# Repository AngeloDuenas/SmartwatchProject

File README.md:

# LVGL project for ESP32

This is an ESP32 demo project showcasing LVGL v7 with support for several display controllers and touch controllers.
The demo application is the `lv_demo_widgets` project from the [lv_examples](https://github.com/lvgl/lv_examples) repository.

- Version of ESP-IDF required 4.2. NOTE: We're trying to make this repo backwards compatible, usage of idf.py is encouraged.
- Version of LVGL used: 7.9.
- Version of lv_examples used: 7.9.

#### Table of content
- [Get started](#get-started)
- [Use LVGL in your ESP-IDF project](#use-lvgl-in-your-esp-idf-project)
- [Use lvgl_esp32_drivers in your project](#use-lvgl_esp32_drivers-in-your-project)
- [Platformio support](#platformio-support)
- [ESP32-S2 Support](#esp32-s2-support)

Example demo for TFT displays:

Monochrome support:

## Display and touch controllers

The display and touch (indev) controllers are now into it's own repository, you can find it [here](https://github.com/lvgl/lvgl_esp32_drivers).
To report any issue or add new display or touch (indev) drivers you can do so in the `lvgl_esp32_drivers` repo.

## Get started

### Prerequisites

- ESP-IDF Framework.

### Note

This project tries to be compatible with both the ESP-IDF v3.x and v4.0, but using v4.0 is recommended.
Instructions assume you are using the v4.x toolchain, otherwise use the make commands, e.g. instead of running `idf.py menuconfig`, run `make menuconfig`.

### Build and run the demo.

1. Clone this project by `git clone --recurse-submodules https://github.com/lvgl/lv_port_esp32.git`, this will pull this repo and its submodules.

2. Get into the created `lv_port_esp32` directory.

3. Run `idf.py menuconfig`

4. Configure LVGL in `Components config->LVGL Configuration`. For monochrome displays use the mono theme and we suggest enabling the `unscii 8` font.

5. Configure your display and/or touch controllers in `Components config->LVGL TFT Display Configuration` and `Components config->LVGL TOUCH Configuration`.

6. Store your project configuration.

7. Build the project with `idf.py build`

8. If the build don't throw any errors, flash the demo with `idf.py -p (YOUR SERIAL PORT) flash` (with `make` this is just `make flash` - in 3.x PORT is configured in `menuconfig`)

## Use LVGL in your ESP-IDF project

LVGL now includes a Kconfig file which is used to configure most of the LVGL configuration options via menuconfig, so it's not necessary to use a custom `lv_conf.h` file.

It is recommended to add LVGL as a submodule in your IDF project's git repo.

From your project's root directory:
1. Create a directory named `components` (if you don't have one already) with `mkdir -p components`.
2. Clone the lvgl repository inside the `components` directory with `git submodule add https://github.com/lvgl/lvgl.git components/lvgl`
3. Run `idf.py menuconfig`, go to `Component config` then `LVGL configuration` to configure LVGL.

## Use lvgl_esp32_drivers in your project

It is recommended to add [lvgl_esp32_drivers](https://github.com/lvgl/lvgl_esp32_drivers) as a submodule in your IDF project's git repo.

From your project's root directory:
1. Create a directory named `components` (if you don't have one already) with `mkdir -p components`.
2. Clone the lvgl_esp32_drivers repository inside the `components` directory with `git submodule add https://github.com/lvgl/lvgl_esp32_drivers.git components/lvgl_esp32_drivers`
3. Run `idf.py menuconfig`, go to `Component config` then `LVGL TFT configuration` and `LVGL TFT Display configuration` to configure lvgl_esp32_drivers.

## Platformio support

Using the [lv_platformio](https://github.com/lvgl/lv_platformio) project add the following lines to `platformio.ini` file:

```
[env:esp32]
platform = espressif32
framework = espidf
board = esp-wrover-kit
```

Change the default environment to `default_envs = esp32`.

Modify the `main.c` like this:

```c
#include "lvgl.h"

// #include "driver.h"

#include "demo.h"

int app_main(void)
{
    lv_init();

    /* Initialize your hardware. */
    
    /* hw_init(); */

    demo_create();

    /* Create the UI or start a task for it.
     * In the end, don't forget to call `lv_task_handler` in a loop. */

    /* hw_loop(); */

    return 0;
}
```

For more information see: [platformio with espidf framework compability](https://github.com/lvgl/lv_port_esp32/issues/168).

# ESP32-S2 Support

Support for ESP32-S2 variant is Work In Progress.
Smaller displays (e.g. 320x240) work fine, but larger ones need testing.

## Background

ESP32-S2 has less on-chip SRAM than its predecessor ESP32 (520kB vs. 320kB).
This causes problems with memory allocation with large LVGL display buffers as they don't fit into the on-chip memory
and external PSRAM is not accessible by DMA.

Moreover, static allocation to external PSRAM is not yet supported
(see [GitHub issue](https://github.com/espressif/esp-idf/issues/6162)).

At this momement, the buffers are dynamicaly allocated with DMA capabilty and memory allocator handles the rest.

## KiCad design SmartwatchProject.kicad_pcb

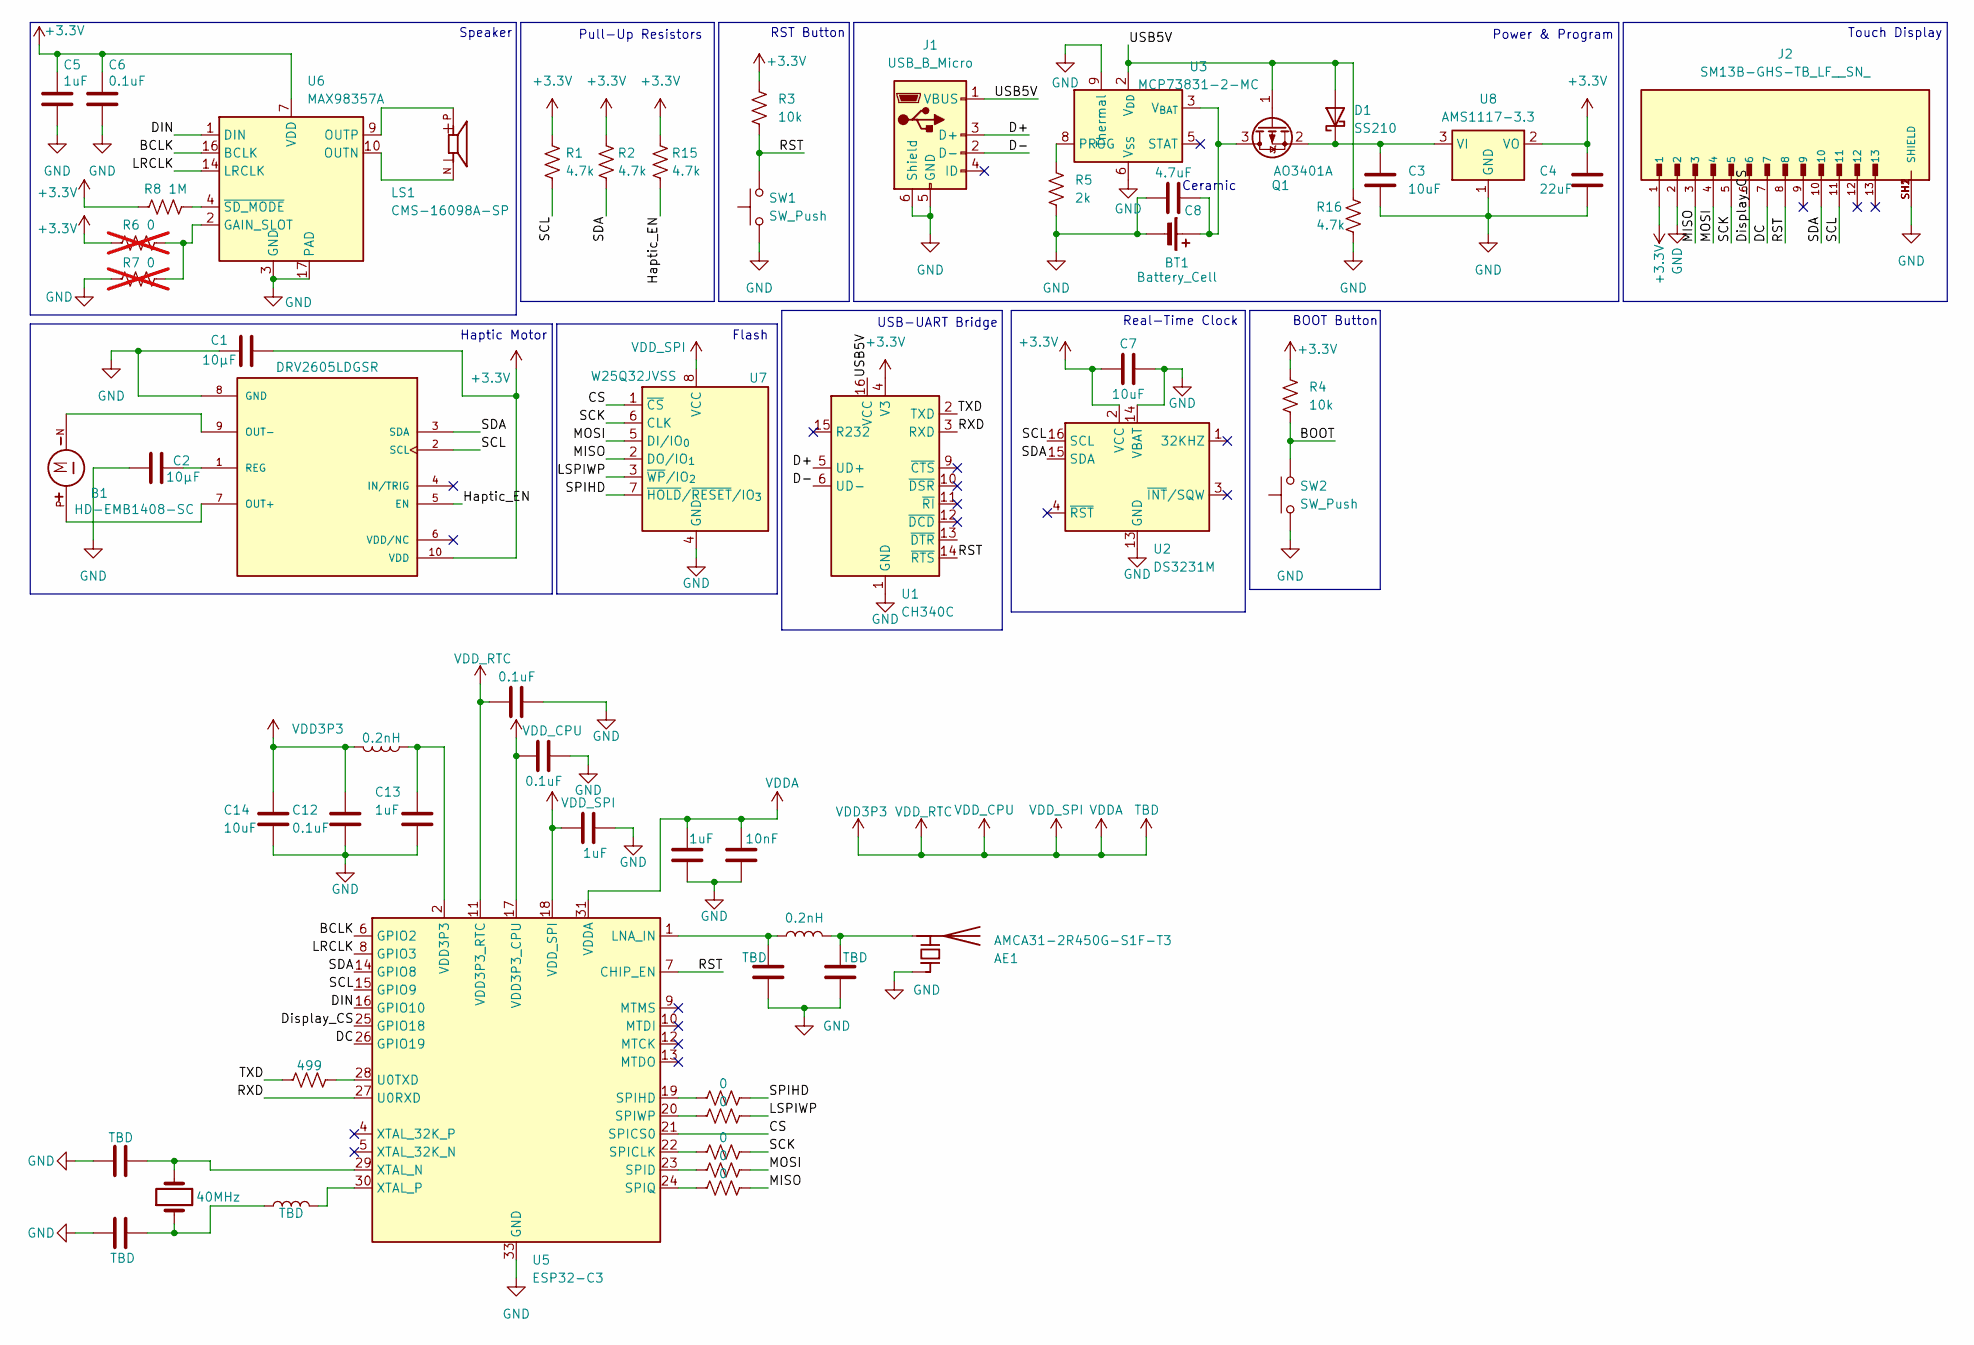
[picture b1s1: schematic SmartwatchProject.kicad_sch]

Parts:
AE1: AMCA31-2R450G-S1F-T3; XDCR_AMCA31-2R450G-S1F-T3
B1: HD-EMB1408-SC; MOTOR_HD-EMB1408-SC; PARTREV A
BT1: Battery_Cell; PinHeader_1x02_P1.00mm_Vertical
C1: 10µF; C_0603_1608Metric
C2: 10µF; C_0402_1005Metric
C3, C7, C14: 10uF; C_0402_1005Metric
C4: 22uF; C_0402_1005Metric
C5, C13, C17, C18: 1uF; C_0402_1005Metric
C6, C12, C15, C16: 0.1uF; C_0402_1005Metric
C8: 4.7uF; C_0402_1005Metric
C10, C11, C20, C21: TBD; C_0402_1005Metric
C19: 10nF; C_0402_1005Metric
D1: SS210; D_SMA
J1: USB_B_Micro; USB_Micro-B_Molex-105017-0001
J2: SM13B-GHS-TB_LF__SN_; JST_SM13B-GHS-TB_LF__SN_; PARTREV 18/3/21
L1, L2: 0.2nH; L_0402_1005Metric
L3: TBD; L_0402_1005Metric
LS1: CMS-16098A-SP; CUI_CMS-16098A-SP
Q1: AO3401A; SOT-23
R1, R2, R15, R16: 4.7k; R_0402_1005Metric
R3, R4: 10k; R_0402_1005Metric
R5: 2k; R_0402_1005Metric
R6, R7: 0; R_0402_1005Metric; not fitted
R8: 1M; R_0402_1005Metric
R9, R10, R11, R12, R13: 0; R_0402_1005Metric
R14: 499; R_0402_1005Metric
SW1, SW2: SW_Push; SW_SPST_TL3342
U1: CH340C; SOIC-16_3.9x9.9mm_P1.27mm
U2: DS3231M; SOIC-16W_7.5x10.3mm_P1.27mm
U3: MCP73831-2-MC; DFN-8-1EP_3x2mm_P0.5mm_EP1.7x1.4mm
U4: DRV2605LDGSR; SOP50P490X110-10N; PARTREV D
U5: ESP32-C3; QFN-32-1EP_5x5mm_P0.5mm_EP3.7x3.7mm
U6: MAX98357A; TQFN-16-1EP_3x3mm_P0.5mm_EP1.23x1.23mm
U7: W25Q32JVSS; SOIC-8_5.3x5.3mm_P1.27mm
U8: AMS1117-3.3; SOT-223-3_TabPin2
Y1: 40MHz; Crystal_SMD_3215-2Pin_3.2x1.5mm

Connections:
+3.3V: C1.2, C4.2, C5.1, C6.1, C7.2, J2.1, R1.1, R2.1, R3.1, R4.1, R6.1, R8.1, R15.1, U1.4 (V3), U2.2 (VCC), U4.10 (VDD), U6.7 (VDD), U6.8 (VDD), U8.2 (VO)
/BCLK: U5.6 (GPIO2), U6.16 (BCLK)
/BOOT: R4.2, SW2.2
/CS: U5.21 (SPICS0), U7.1 (~CS)
/D+: J1.3 (D+), U1.5 (UD+)
/D-: J1.2 (D-), U1.6 (UD-)
/DC: J2.7, U5.26 (GPIO19)
/DIN: U5.16 (GPIO10), U6.1 (DIN)
/Display_CS: J2.6, U5.25 (GPIO18)
/Haptic_EN: R15.2, U4.5 (EN)
/LRCLK: U5.8 (GPIO3), U6.14 (LRCLK)
/LSPIWP: R10.2, U7.3 (~WP/IO_{2})
/MISO: J2.3, R13.2, U7.2 (DO/IO_{1})
/MOSI: J2.4, R12.2, U7.5 (DI/IO_{0})
/RST: J2.8, R3.2, SW1.2, U1.14 (~RTS), U5.7 (CHIP_EN)
/RXD: U1.3 (RXD), U5.27 (U0RXD)
/SCK: J2.5, R11.2, U7.6 (CLK)
/SCL: J2.11, R1.2, U2.16 (SCL), U4.2 (SCL), U5.15 (GPIO9)
/SDA: J2.10, R2.2, U2.15 (SDA), U4.3 (SDA), U5.14 (GPIO8)
/SPIHD: R9.2, U7.7 (~HOLD/~RESET/IO_{3})
/TXD: R14.1, U1.2 (TXD)
/USB5V: D1.2 (A), J1.1 (VBUS), Q1.1 (G), R16.1, U1.16 (VCC), U3.1 (V_{DD}), U3.2 (V_{DD})
GND: AE1.1 (FEED), BT1.2 (-), C1.1, C2.1, C3.2, C4.1, C5.2, C6.2, C7.1, C8.2, C10.2, C11.2, C12.2, C13.2, C14.2, C15.2, C16.2, C17.2, C18.1, C19.1, C20.2, C21.2, J1.5 (GND), J1.6 (Shield), J2.2, J2.SH1 (SHIELD), J2.SH2 (SHIELD), R5.2, R7.1, R16.2, SW1.1, SW2.1, U1.1 (GND), U2.5 (GND), U2.6 (GND), U2.7 (GND), U2.8 (GND), U2.9 (GND), U2.10 (GND), U2.11 (GND), U2.12 (GND), U2.13 (GND), U2.14 (VBAT), U3.6 (V_{SS}), U3.9 (Thermal), U4.8 (GND), U5.33 (GND), U6.3 (GND), U6.11 (GND), U6.15 (GND), U6.17 (PAD), U7.4 (GND), U8.1 (GND)
unnamed: AE1.2 (PCB_Trace), C11.1, L1.2
unnamed: BT1.1 (+), C8.1, Q1.3 (D), U3.3 (V_{BAT}), U3.4 (V_{BAT})
unnamed: C13.1, L2.1, U5.2 (VDD3P3), U5.3 (VDD3P3)
unnamed: C21.1, L3.1, Y1.1
unnamed: C3.1, D1.1 (K), Q1.2 (S), U8.3 (VI)
unnamed: R5.1, U3.8 (PROG)
unnamed: B1.P, U4.7 (OUT+)
unnamed: B1.N, U4.9 (OUT-)
unnamed: C2.2, U4.1 (REG)
unnamed: C10.1, L1.1, U5.1 (LNA_IN)
unnamed: R11.1, U5.22 (SPICLK)
unnamed: R12.1, U5.23 (SPID)
unnamed: R9.1, U5.19 (SPIHD)
unnamed: R13.1, U5.24 (SPIQ)
unnamed: R10.1, U5.20 (SPIWP)
unnamed: R14.2, U5.28 (U0TXD)
unnamed: C20.1, U5.29 (XTAL_N), Y1.2
unnamed: L3.2, U5.30 (XTAL_P)
unnamed: R6.2, R7.2, U6.2 (GAIN_SLOT)
unnamed: LS1.N, U6.10 (OUTN)
unnamed: LS1.P, U6.9 (OUTP)
unnamed: R8.2, U6.4 (~SD_MODE)
TBD: C12.1, C14.1, C15.1, C16.1, C17.1, C18.2, C19.2, L2.2, U5.11 (VDD3P3_RTC), U5.17 (VDD3P3_CPU), U5.18 (VDD_SPI), U5.31 (VDDA), U5.32 (VDDA), U7.8 (VCC)

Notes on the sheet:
Pull-Up Resistors
Real-Time Clock
Haptic Motor
Speaker
Flash
USB-UART Bridge
RST Button
Ceramic
Touch Display
BOOT Button
Power & Program

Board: 2 copper layers, 58 parts (0 on the bottom side), 46 nets, no tracks yet.

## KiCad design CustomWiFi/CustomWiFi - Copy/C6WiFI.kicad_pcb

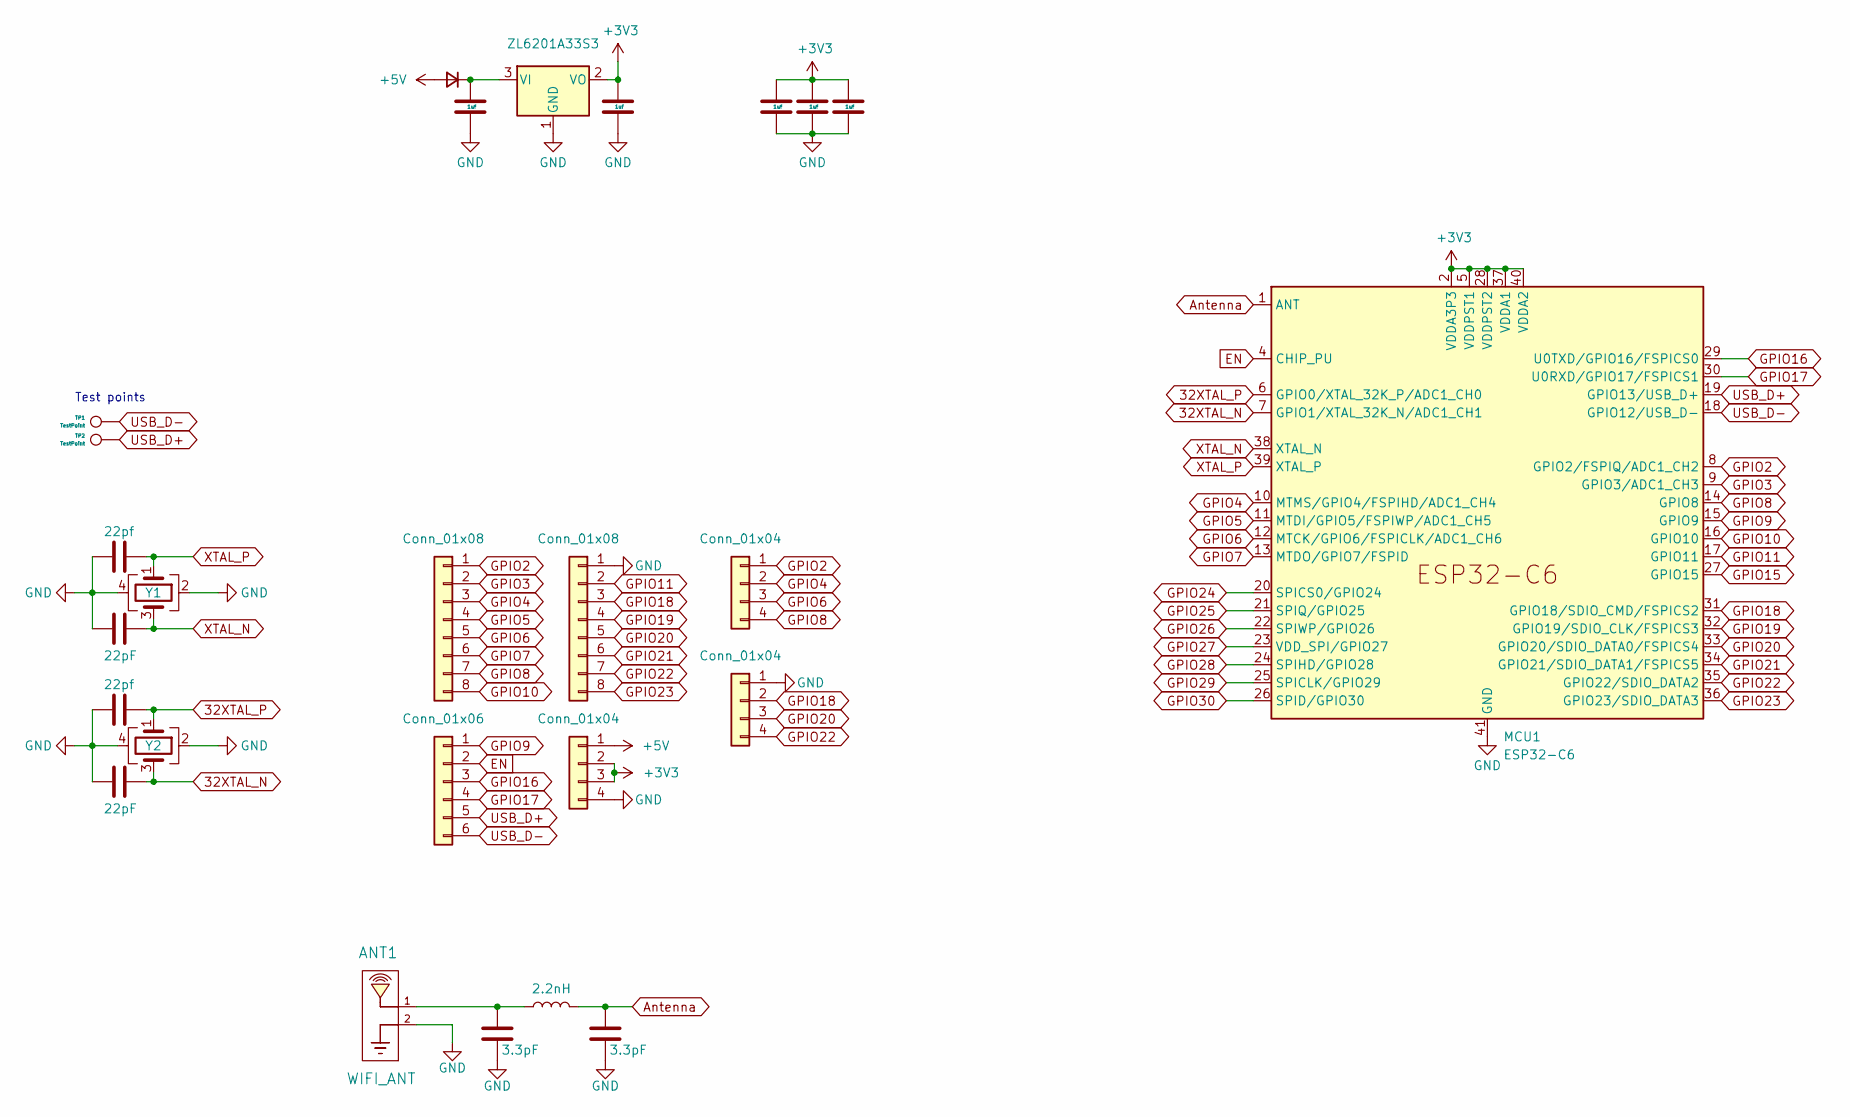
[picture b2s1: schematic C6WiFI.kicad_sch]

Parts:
ANT1: WIFI_ANT; Texas_SWRA117D_2.4GHz_Left
C1, C2, C7, C8, C10: 1uf; C_0402_1005Metric
C3, C5: 22pf; C_0402_1005Metric
C4, C6: 22pF; C_0402_1005Metric
C12, C13: 3.3pF; C_0201_0603Metric
D1: SOD-523 General; D_SOD-523
J1: Conn_01x06; PinHeader_1x06_P1.27mm_Vertical
J2, J3: Conn_01x08; PinHeader_1x08_P1.27mm_Vertical
J4, J6: Conn_01x04; PinHeader_1x04_P2.54mm_Vertical
J5: Conn_01x04; PinHeader_1x04_P1.27mm_Vertical
L1: 2.2nH; L_0201_0603Metric
MCU1: ESP32-C6; QFN-40-1EP_5x5mm_P0.4mm_EP3.6x3.6mm
TP1, TP2: TestPoint; TestPoint_Pad_D1.5mm
U2: ZL6201A33S3; SOT-23
Y1: 2016-4P 40MHz; Crystal_SMD_2016-4Pin_2.0x1.6mm; LCSC OT201640MJBA4SL
Y2: SX2M32.768KM20F30TNN; Crystal_SMD_2520-4Pin_2.5x2.0mm

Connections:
32XTAL_N: C6.1, MCU1.7 (GPIO1/XTAL_32K_N/ADC1_CH1), Y2.3
32XTAL_P: C5.1, MCU1.6 (GPIO0/XTAL_32K_P/ADC1_CH0), Y2.1
+3V3: C2.1, C7.1, C8.1, C10.1, J5.2, J5.3, MCU1.2 (VDDA3P3), MCU1.3 (VDDA3P3), MCU1.5 (VDDPST1), MCU1.28 (VDDPST2), MCU1.37 (VDDA1), MCU1.40 (VDDA2), U2.2 (VO)
+5V: D1.2 (A), J5.1
Antenna: C13.1, L1.2, MCU1.1 (ANT)
EN: J1.2, MCU1.4 (CHIP_PU)
GND: ANT1.2, C1.2, C2.2, C3.2, C4.2, C5.2, C6.2, C7.2, C8.2, C10.2, C12.2, C13.2, J3.1, J5.4, J6.1, MCU1.41 (GND), U2.1 (GND), Y1.2, Y1.4, Y2.2, Y2.4
GPIO2: J2.1, J4.1, MCU1.8 (GPIO2/FSPIQ/ADC1_CH2)
GPIO3: J2.2, MCU1.9 (GPIO3/ADC1_CH3)
GPIO4: J2.3, J4.2, MCU1.10 (MTMS/GPIO4/FSPIHD/ADC1_CH4)
GPIO5: J2.4, MCU1.11 (MTDI/GPIO5/FSPIWP/ADC1_CH5)
GPIO6: J2.5, J4.3, MCU1.12 (MTCK/GPIO6/FSPICLK/ADC1_CH6)
GPIO7: J2.6, MCU1.13 (MTDO/GPIO7/FSPID)
GPIO8: J2.7, J4.4, MCU1.14 (GPIO8)
GPIO9: J1.1, MCU1.15 (GPIO9)
GPIO10: J2.8, MCU1.16 (GPIO10)
GPIO11: J3.2, MCU1.17 (GPIO11)
GPIO15: MCU1.27 (GPIO15)
GPIO16: J1.3, MCU1.29 (U0TXD/GPIO16/FSPICS0)
GPIO17: J1.4, MCU1.30 (U0RXD/GPIO17/FSPICS1)
GPIO18: J3.3, J6.2, MCU1.31 (GPIO18/SDIO_CMD/FSPICS2)
GPIO19: J3.4, MCU1.32 (GPIO19/SDIO_CLK/FSPICS3)
GPIO20: J3.5, J6.3, MCU1.33 (GPIO20/SDIO_DATA0/FSPICS4)
GPIO21: J3.6, MCU1.34 (GPIO21/SDIO_DATA1/FSPICS5)
GPIO22: J3.7, J6.4, MCU1.35 (GPIO22/SDIO_DATA2)
GPIO23: J3.8, MCU1.36 (GPIO23/SDIO_DATA3)
GPIO24: MCU1.20 (SPICS0/GPIO24)
GPIO25: MCU1.21 (SPIQ/GPIO25)
GPIO26: MCU1.22 (SPIWP/GPIO26)
GPIO27: MCU1.23 (VDD_SPI/GPIO27)
GPIO28: MCU1.24 (SPIHD/GPIO28)
GPIO29: MCU1.25 (SPICLK/GPIO29)
GPIO30: MCU1.26 (SPID/GPIO30)
unnamed: ANT1.1, C12.1, L1.1
unnamed: C1.1, D1.1 (K), U2.3 (VI)
USB_D+: J1.5, MCU1.19 (GPIO13/USB_D+), TP2.1
USB_D-: J1.6, MCU1.18 (GPIO12/USB_D-), TP1.1
XTAL_N: C4.1, MCU1.38 (XTAL_N), Y1.3
XTAL_P: C3.1, MCU1.39 (XTAL_P), Y1.1

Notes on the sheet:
Test points

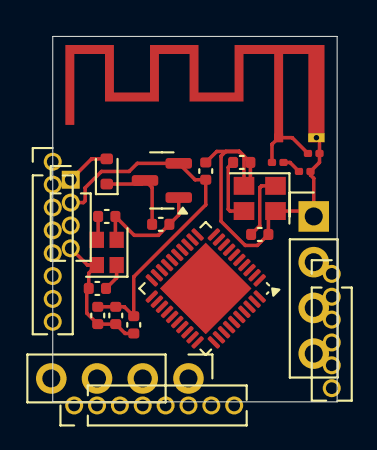
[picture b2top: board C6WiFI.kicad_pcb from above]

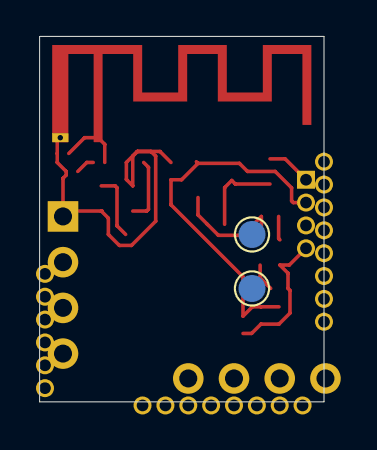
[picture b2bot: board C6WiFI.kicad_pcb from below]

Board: 2 copper layers, 15.8 x 20.3 mm, 26 parts (2 on the bottom side), 31 nets.

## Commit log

2025-06-07 FirstCommit
2025-06-07 Net update
2025-06-07 SecondCommit
2025-06-07 ThirdCommit
2025-06-07 Some small edits
2025-06-07 FourthCommit
2025-06-08 FifthCommit
2025-06-08 SixthCommit
2025-06-22 Schematic Update
2025-06-22 Display
2025-08-30 Revert "testing_v1"
2025-09-01 configuration
2025-09-01 small changes
2025-09-01 PCB Draft
2025-09-02 Schematic Draft
